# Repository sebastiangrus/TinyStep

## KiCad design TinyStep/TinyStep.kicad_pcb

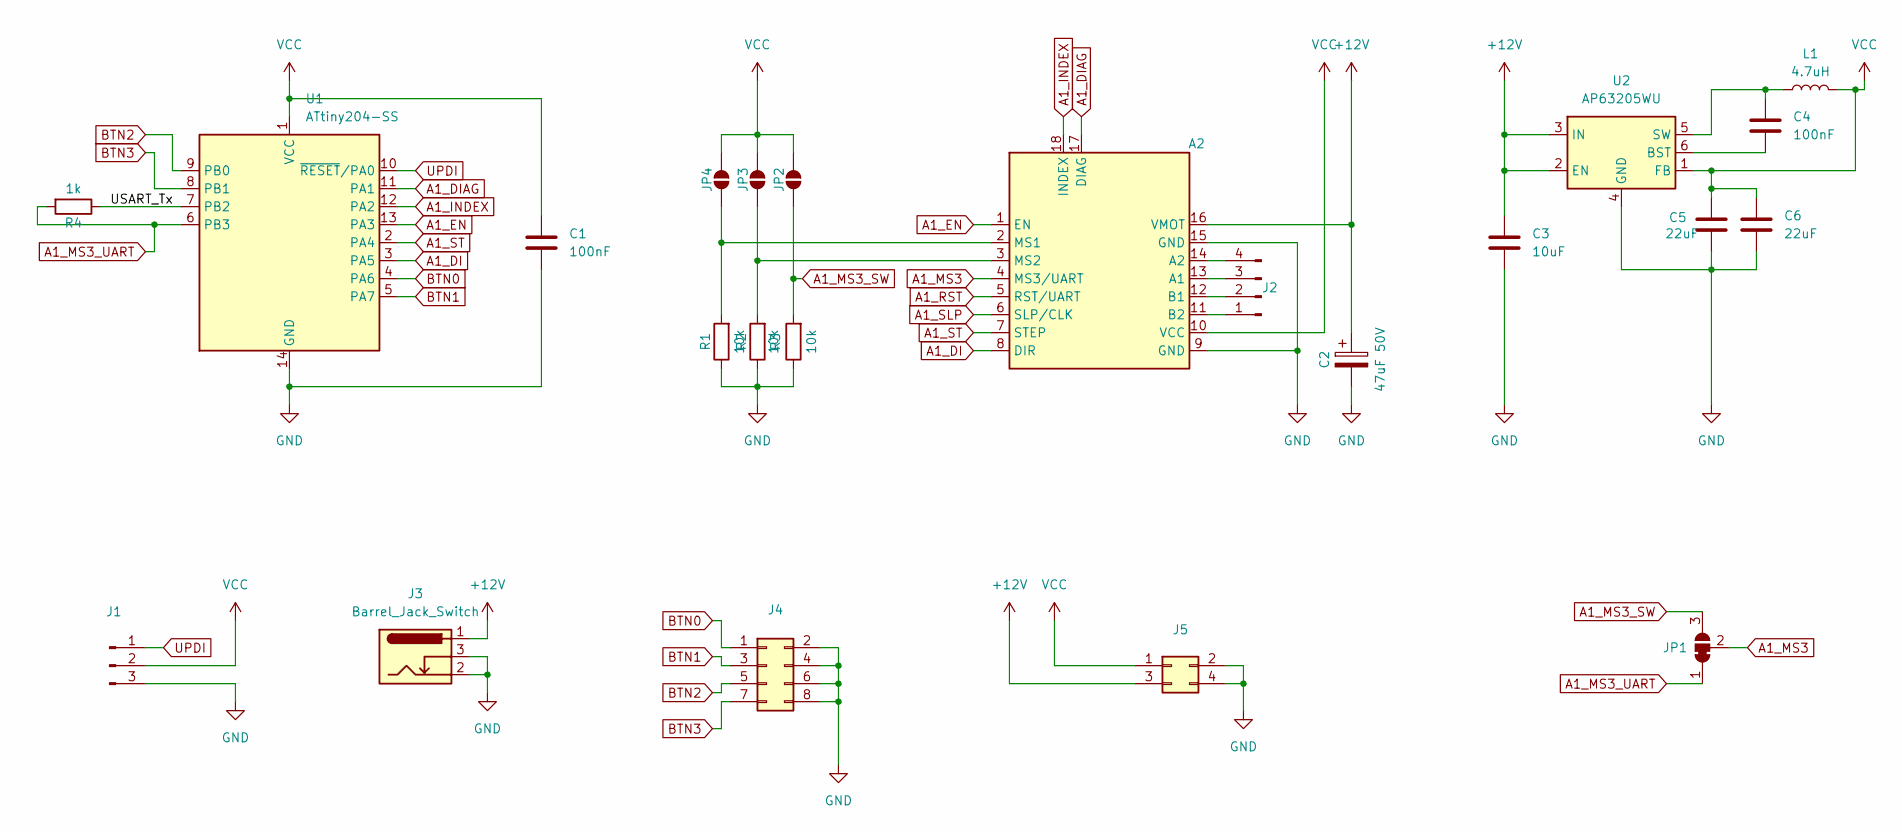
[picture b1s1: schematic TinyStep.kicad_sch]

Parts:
A2: TMC2209_BTT
C1, C4: 100nF; C_0805_2012Metric_Pad1.18x1.45mm_HandSolder
C2: 47uF 50V; CP_Elec_6.3x7.7
C3: 10uF; C_0805_2012Metric_Pad1.18x1.45mm_HandSolder
C5, C6: 22uF; C_0805_2012Metric_Pad1.18x1.45mm_HandSolder
J1: Conn_01x03_Pin; PinHeader_1x03_P2.54mm_Vertical
J2: Conn_01x04_Pin; JST_XH_S4B-XH-A_1x04_P2.50mm_Horizontal
J3: Barrel_Jack_Switch; BarrelJack_Wuerth_6941xx301002
J4: Conn_02x04_Odd_Even; PinHeader_2x04_P2.54mm_Vertical
J5: Conn_02x02_Odd_Even; PinHeader_2x02_P2.54mm_Vertical
JP1: SolderJumper_3_Bridged12; SolderJumper-3_P1.3mm_Bridged12_RoundedPad1.0x1.5mm_NumberL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
JP2, JP3, JP4: SolderJumper_2_Open; SolderJumper-2_P1.3mm_Open_RoundedPad1.0x1.5mm
L1: 4.7uH; L_0805_2012Metric_Pad1.15x1.40mm_HandSolder
R1, R2, R3: 10k; R_0805_2012Metric_Pad1.20x1.40mm_HandSolder
R4: 1k; R_0805_2012Metric_Pad1.20x1.40mm_HandSolder
U1: ATtiny204-SS; SOIC-14_3.9x8.7mm_P1.27mm
U2: AP63205WU; TSOT-23-6

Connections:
+12V: A2.16 (VMOT), C2.1, C3.1, J3.1, J5.3, U2.2 (EN), U2.3 (IN)
/USART_Tx: R4.1, U1.7 (PB2)
A1_DI: A2.8 (DIR), U1.3 (PA5)
A1_DIAG: A2.17 (DIAG), U1.11 (PA1)
A1_EN: A2.1 (EN), U1.13 (PA3)
A1_INDEX: A2.18 (INDEX), U1.12 (PA2)
A1_MS3: A2.4 (MS3/UART), JP1.2 (C)
A1_MS3_SW: JP1.3 (B), JP2.1 (A), R3.2
A1_MS3_UART: JP1.1 (A), R4.2, U1.6 (PB3)
A1_RST: A2.5 (RST/UART)
A1_SLP: A2.6 (SLP/CLK)
A1_ST: A2.7 (STEP), U1.2 (PA4)
BTN0: J4.1, U1.4 (PA6)
BTN1: J4.3, U1.5 (PA7)
BTN2: J4.5, U1.9 (PB0)
BTN3: J4.7, U1.8 (PB1)
GND: A2.9 (GND), A2.15 (GND), C1.2, C2.2, C3.2, C5.2, C6.2, J1.3, J3.2, J3.3, J4.2, J4.4, J4.6, J4.8, J5.2, J5.4, R1.1, R2.1, R3.1, U1.14 (GND), U2.4 (GND)
unnamed: A2.13 (A1), J2.3
unnamed: A2.14 (A2), J2.4
unnamed: A2.12 (B1), J2.2
unnamed: A2.11 (B2), J2.1
unnamed: A2.2 (MS1), JP4.1 (A), R1.2
unnamed: A2.3 (MS2), JP3.1 (A), R2.2
unnamed: C4.2, U2.6 (BST)
unnamed: C4.1, L1.1, U2.5 (SW)
UPDI: J1.1, U1.10 (~RESET/PA0)
VCC: A2.10 (VCC), C1.1, C5.1, C6.1, J1.2, J5.1, JP2.2 (B), JP3.2 (B), JP4.2 (B), L1.2, U1.1 (VCC), U2.1 (FB)

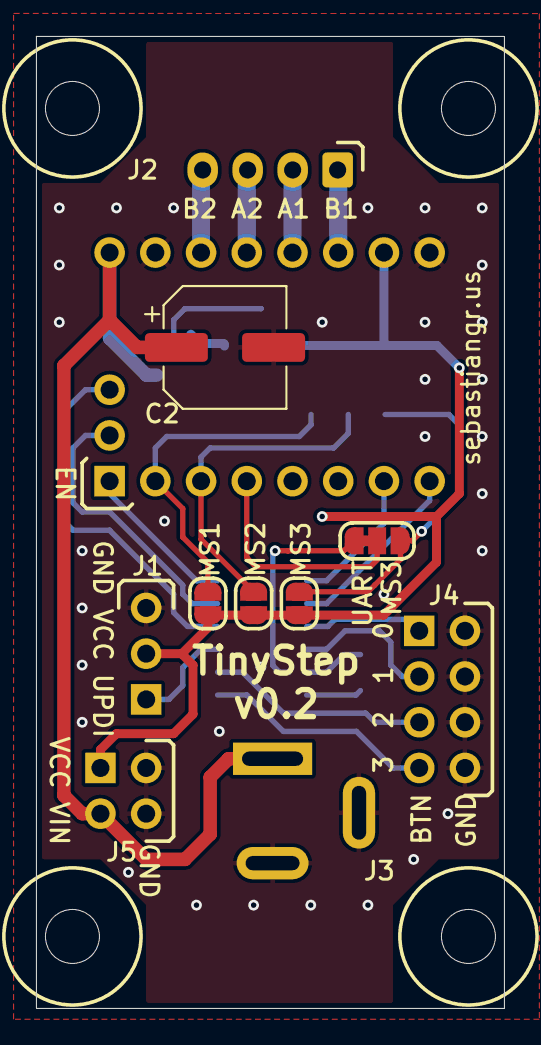
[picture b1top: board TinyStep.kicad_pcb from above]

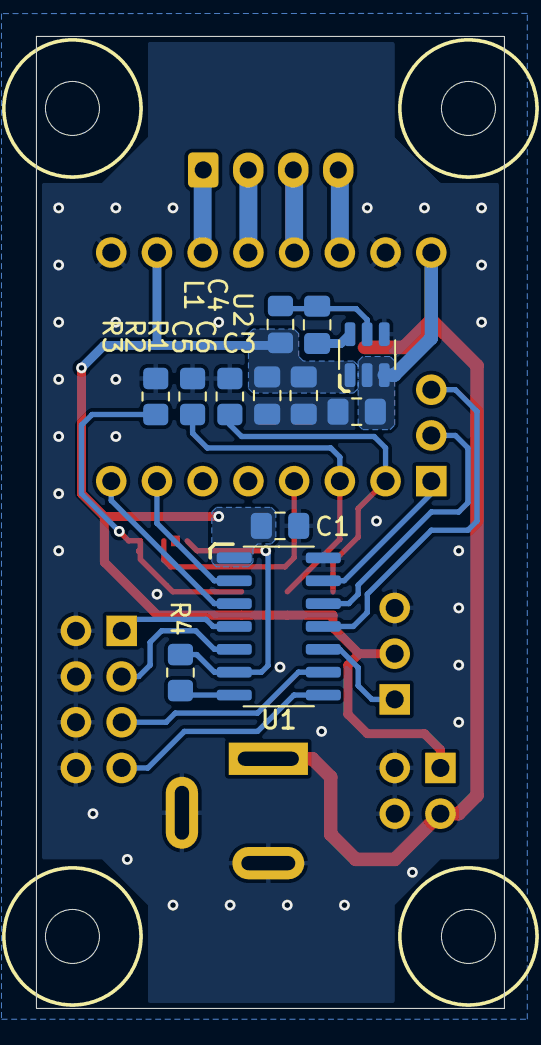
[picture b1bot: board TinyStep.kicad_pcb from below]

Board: 2 copper layers, 26.0 x 54.0 mm, 23 parts (12 on the bottom side), 25 nets.

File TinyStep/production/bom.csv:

Designator,Footprint,Quantity,Value,LCSC Part #
A2,TMC2209_BTT,1,~,
"C1, C4",0805,2,100nF,
C2,CP_Elec_6.3x7.7,1,47uF 50V,
C3,0805,1,10uF,
"C5, C6",0805,2,22uF,
J1,PinHeader_1x03_P2.54mm_Vertical,1,Conn_01x03_Pin,
J2,JST_XH_S4B-XH-A_1x04_P2.50mm_Horizontal,1,Conn_01x04_Pin,
J3,BarrelJack_Wuerth_6941xx301002,1,Barrel_Jack_Switch,
J4,PinHeader_2x05_P2.54mm_Vertical,1,Conn_02x05_Odd_Even,
J5,PinHeader_2x02_P2.54mm_Vertical,1,Conn_02x02_Odd_Even,
L1,0805,1,4.7uH,
"R1, R2, R3",0805,3,10k,
R4,0805,1,1k,
U1,SOIC-14_3.9x8.7mm_P1.27mm,1,ATtiny204-SS,
U2,TSOT-23-6,1,AP63205WU,

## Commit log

2024-07-28 huge 1st commit
2024-07-31 this might work
2024-08-11 v0.1
2024-08-11 v0.1 production
2024-08-11 backups
2024-10-09 GND vias, cleaner board
2026-03-05 HT42B534 library
